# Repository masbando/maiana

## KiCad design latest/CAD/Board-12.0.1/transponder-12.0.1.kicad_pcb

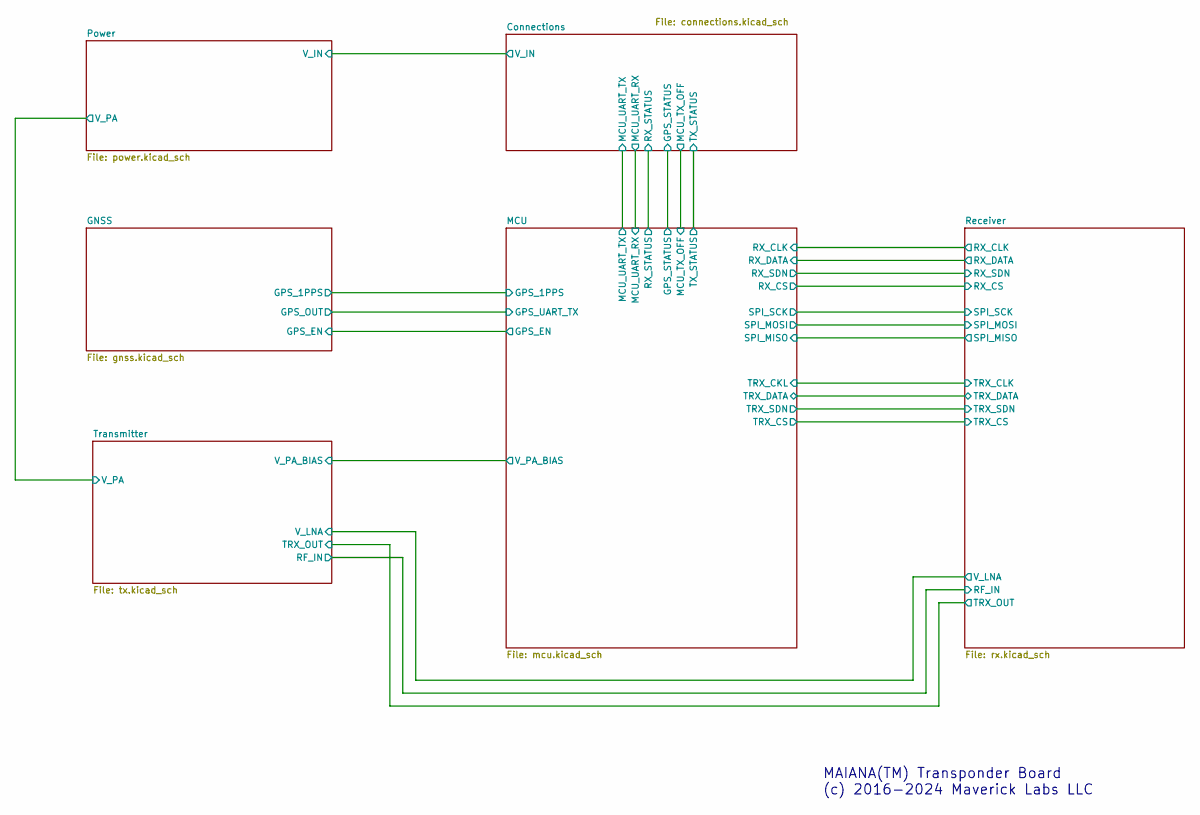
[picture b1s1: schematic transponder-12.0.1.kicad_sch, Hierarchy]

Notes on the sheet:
MAIANA(TM) Transponder Board (c) 2016-2024 Maverick Labs LLC

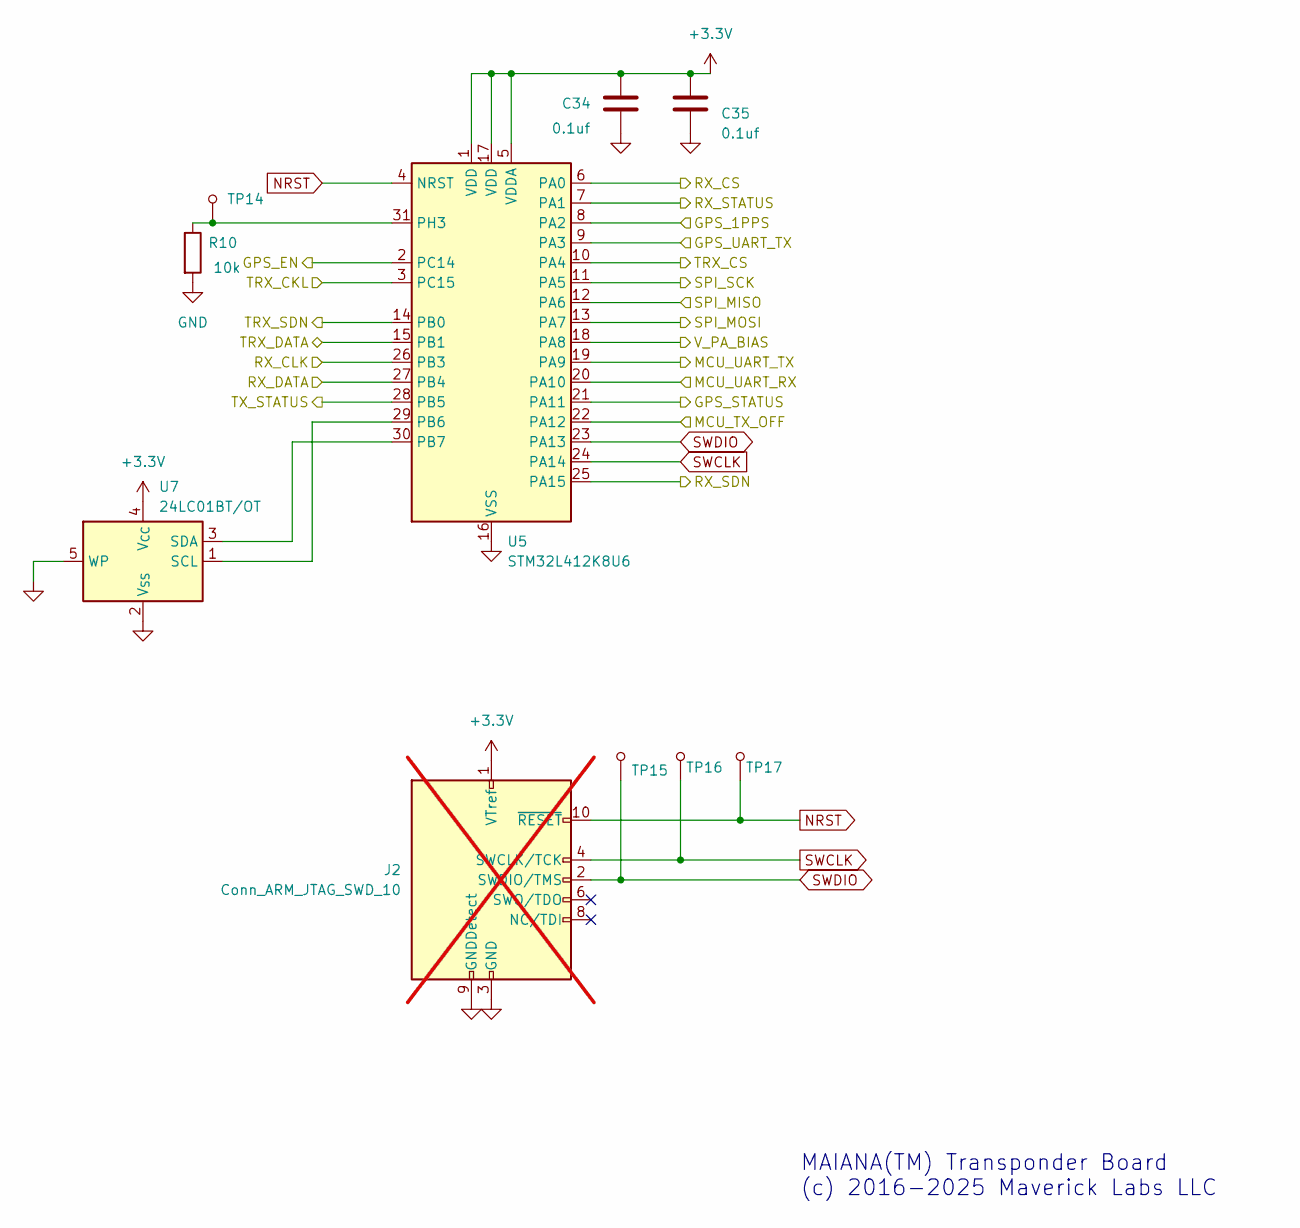
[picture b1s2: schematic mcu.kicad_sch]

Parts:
C34, C35: 0.1uf; C_0603_1608Metric
J2: Conn_ARM_JTAG_SWD_10; PinHeader_2x05_P1.27mm_Vertical_SMD; not fitted
R10: 10k; R_0603_1608Metric
TP14, TP15, TP16, TP17: TP_1.2MM
U5: STM32L412K8U6; QFN-32-1EP_5x5mm_P0.5mm_EP3.45x3.45mm
U7: 24LC01BT/OT; SOT-23-5

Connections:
+3.3V: C34.2, C35.2, J2.1 (VTref), U5.1 (VDD), U5.5 (VDDA), U5.17 (VDD), U7.4 (V_{CC}); also elsewhere on the board
/Connections/GPS_STATUS: U5.21 (PA11); also elsewhere on the board
/Connections/MCU_TX_OFF: U5.22 (PA12); also elsewhere on the board
/Connections/MCU_UART_RX: U5.20 (PA10); also elsewhere on the board
/Connections/MCU_UART_TX: U5.19 (PA9); also elsewhere on the board
/Connections/RX_STATUS: U5.7 (PA1); also elsewhere on the board
/Connections/TX_STATUS: U5.28 (PB5); also elsewhere on the board
/GNSS/GPS_1PPS: U5.8 (PA2); also elsewhere on the board
/GNSS/GPS_EN: U5.2 (PC14); also elsewhere on the board
/GNSS/GPS_OUT: U5.9 (PA3); also elsewhere on the board
/MCU/RX_CLK: U5.26 (PB3); also elsewhere on the board
/MCU/RX_CS: U5.6 (PA0); also elsewhere on the board
/MCU/RX_DATA: U5.27 (PB4); also elsewhere on the board
/MCU/RX_SDN: U5.25 (PA15); also elsewhere on the board
/MCU/SPI_MISO: U5.12 (PA6); also elsewhere on the board
/MCU/SPI_MOSI: U5.13 (PA7); also elsewhere on the board
/MCU/SPI_SCK: U5.11 (PA5); also elsewhere on the board
/MCU/TRX_CKL: U5.3 (PC15); also elsewhere on the board
/MCU/TRX_CS: U5.10 (PA4); also elsewhere on the board
/MCU/TRX_DATA: U5.15 (PB1); also elsewhere on the board
/MCU/TRX_SDN: U5.14 (PB0); also elsewhere on the board
/MCU/V_PA_BIAS: U5.18 (PA8); also elsewhere on the board
GND: C34.1, C35.1, J2.3 (GND), J2.5 (GND), J2.9 (GNDDetect), R10.2, U5.16 (VSS), U5.32 (VSS), U5.33 (VSS), U7.2 (V_{SS}), U7.5 (WP); also elsewhere on the board
NRST: J2.10 (~RESET), TP17.1, U5.4 (NRST)
unnamed: R10.1, TP14.1, U5.31 (PH3)
unnamed: U5.29 (PB6), U7.1 (SCL)
unnamed: U5.30 (PB7), U7.3 (SDA)
SWCLK: J2.4 (SWCLK/TCK), TP16.1, U5.24 (PA14)
SWDIO: J2.2 (SWDIO/TMS), TP15.1, U5.23 (PA13)

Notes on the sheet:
MAIANA(TM) Transponder Board (c) 2016-2025 Maverick Labs LLC

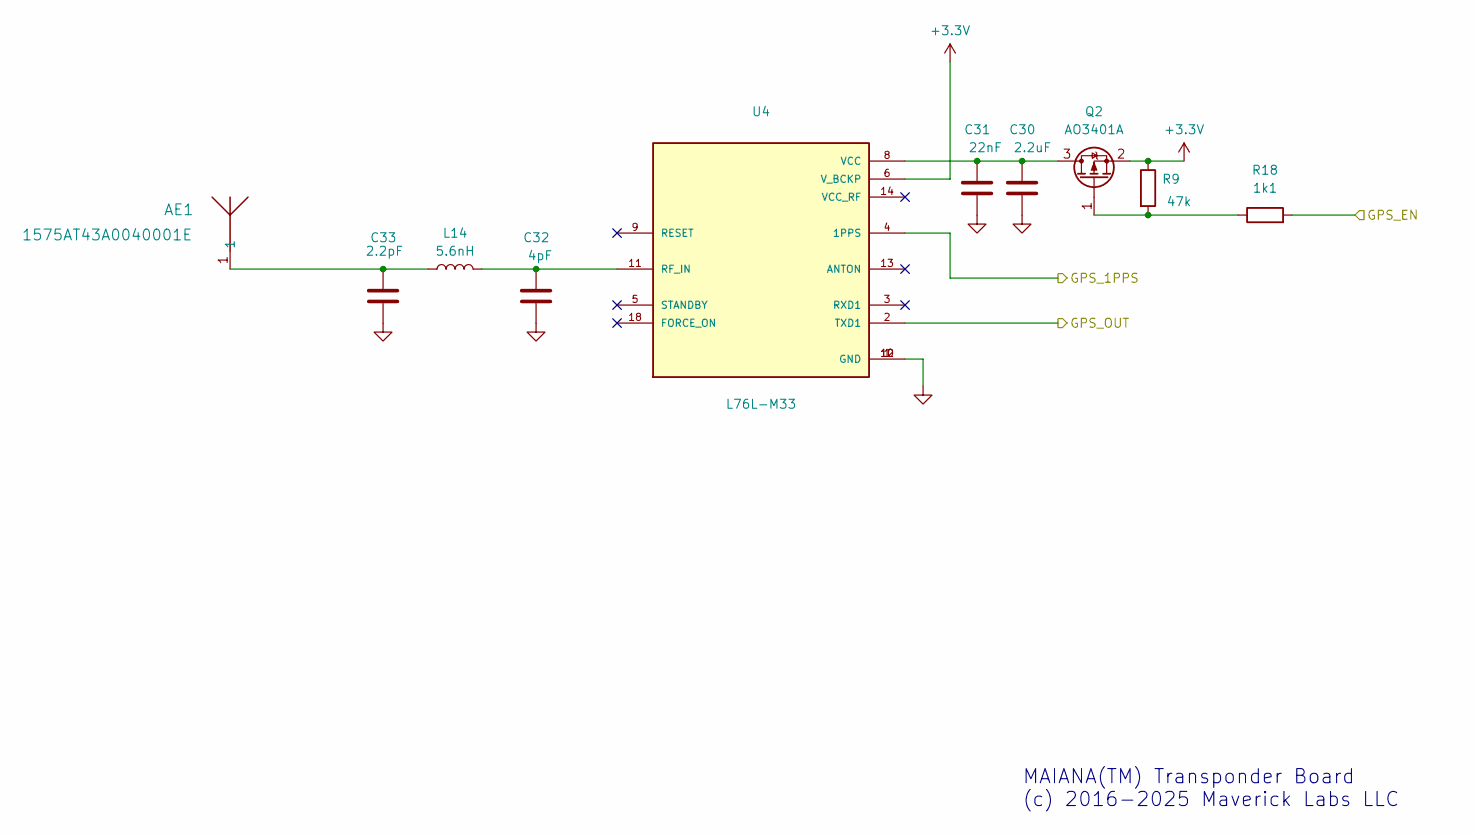
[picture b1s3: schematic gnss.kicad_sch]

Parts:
AE1: 1575AT43A0040001E; ANT_1575AT_JOT
C30: 2.2uF; C_0603_1608Metric
C31: 22nF; C_0603_1608Metric
C32: 4pF; C_0603_1608Metric
C33: 2.2pF; C_0603_1608Metric
L14: 5.6nH; L_0603_1608Metric
Q2: AO3401A; SOT-23
R9: 47k; R_0603_1608Metric
R18: 1k1; R_0603_1608Metric
U4: L76L-M33; XCVR_L76L-M33

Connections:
+3.3V: Q2.2 (S), R9.1, U4.6 (V_BCKP); also elsewhere on the board
/GNSS/GPS_1PPS: U4.4 (1PPS); also elsewhere on the board
/GNSS/GPS_EN: R18.2; also elsewhere on the board
/GNSS/GPS_OUT: U4.2 (TXD1); also elsewhere on the board
GND: C30.1, C31.1, C32.1, C33.1, U4.1 (GND), U4.10 (GND), U4.12 (GND); also elsewhere on the board
unnamed: AE1.1, C33.2, L14.1
unnamed: C30.2, C31.2, Q2.3 (D), U4.8 (VCC)
unnamed: Q2.1 (G), R9.2, R18.1
unnamed: C32.2, L14.2, U4.11 (RF_IN)

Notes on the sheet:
MAIANA(TM) Transponder Board (c) 2016-2025 Maverick Labs LLC

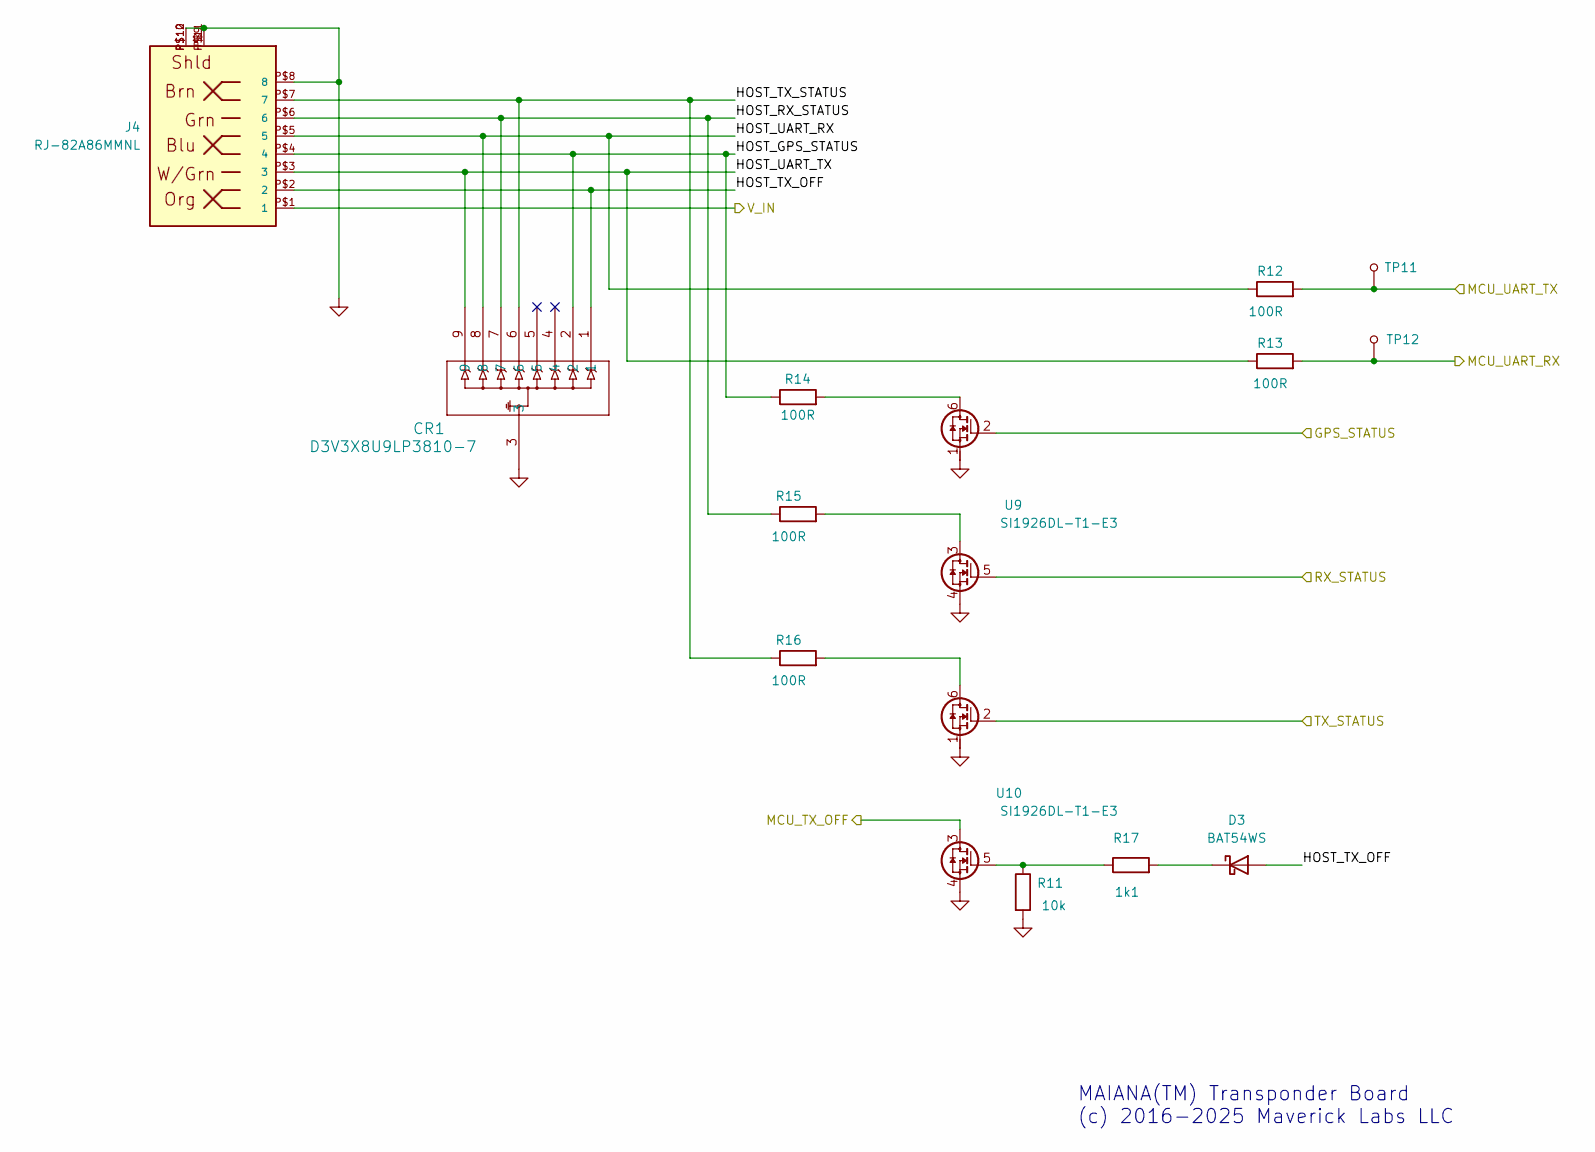
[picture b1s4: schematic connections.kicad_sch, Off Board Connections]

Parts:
CR1: D3V3X8U9LP3810-7; U-DFN3810-9TYPE_B_DIO
D3: BAT54WS; D_SOD-323
J4: RJ-82A86MMNL; PARTNO RJ-82A86MMNL
R11: 10k; R_0603_1608Metric
R12, R13, R14, R15, R16: 100R; R_0603_1608Metric
R17: 1k1; R_0603_1608Metric
TP11, TP12: TP_1.2MM
U9, U10: SI1926DL-T1-E3; SOT-363_SC-70-6

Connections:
/Connections/GPS_STATUS: U9.2 (G1); also elsewhere on the board
/Connections/HOST_GPS_STATUS: CR1.2, J4.P$4 (4), R14.1
/Connections/HOST_RX_STATUS: CR1.7, J4.P$6 (6), R15.1
/Connections/HOST_TX_OFF: CR1.1, D3.2 (A), J4.P$2 (2)
/Connections/HOST_TX_STATUS: CR1.6, J4.P$7 (7), R16.1
/Connections/HOST_UART_RX: CR1.8, J4.P$5 (5), R12.1
/Connections/HOST_UART_TX: CR1.9, J4.P$3 (3), R13.1
/Connections/MCU_TX_OFF: U10.3 (D2); also elsewhere on the board
/Connections/MCU_UART_RX: R13.2, TP12.1; also elsewhere on the board
/Connections/MCU_UART_TX: R12.2, TP11.1; also elsewhere on the board
/Connections/RX_STATUS: U9.5 (G2); also elsewhere on the board
/Connections/TX_STATUS: U10.2 (G1); also elsewhere on the board
/Connections/V_IN: J4.P$1 (1); also elsewhere on the board
GND: CR1.3, J4.P$8 (8), J4.P$9, J4.P$10, J4.P$11, J4.P$12, R11.2, U9.1 (S1), U9.4 (S2), U10.1 (S1), U10.4 (S2); also elsewhere on the board
unnamed: D3.1 (K), R17.2
unnamed: R14.2, U9.6 (D1)
unnamed: R15.2, U9.3 (D2)
unnamed: R16.2, U10.6 (D1)
unnamed: R11.1, R17.1, U10.5 (G2)

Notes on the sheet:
MAIANA(TM) Transponder Board (c) 2016-2025 Maverick Labs LLC

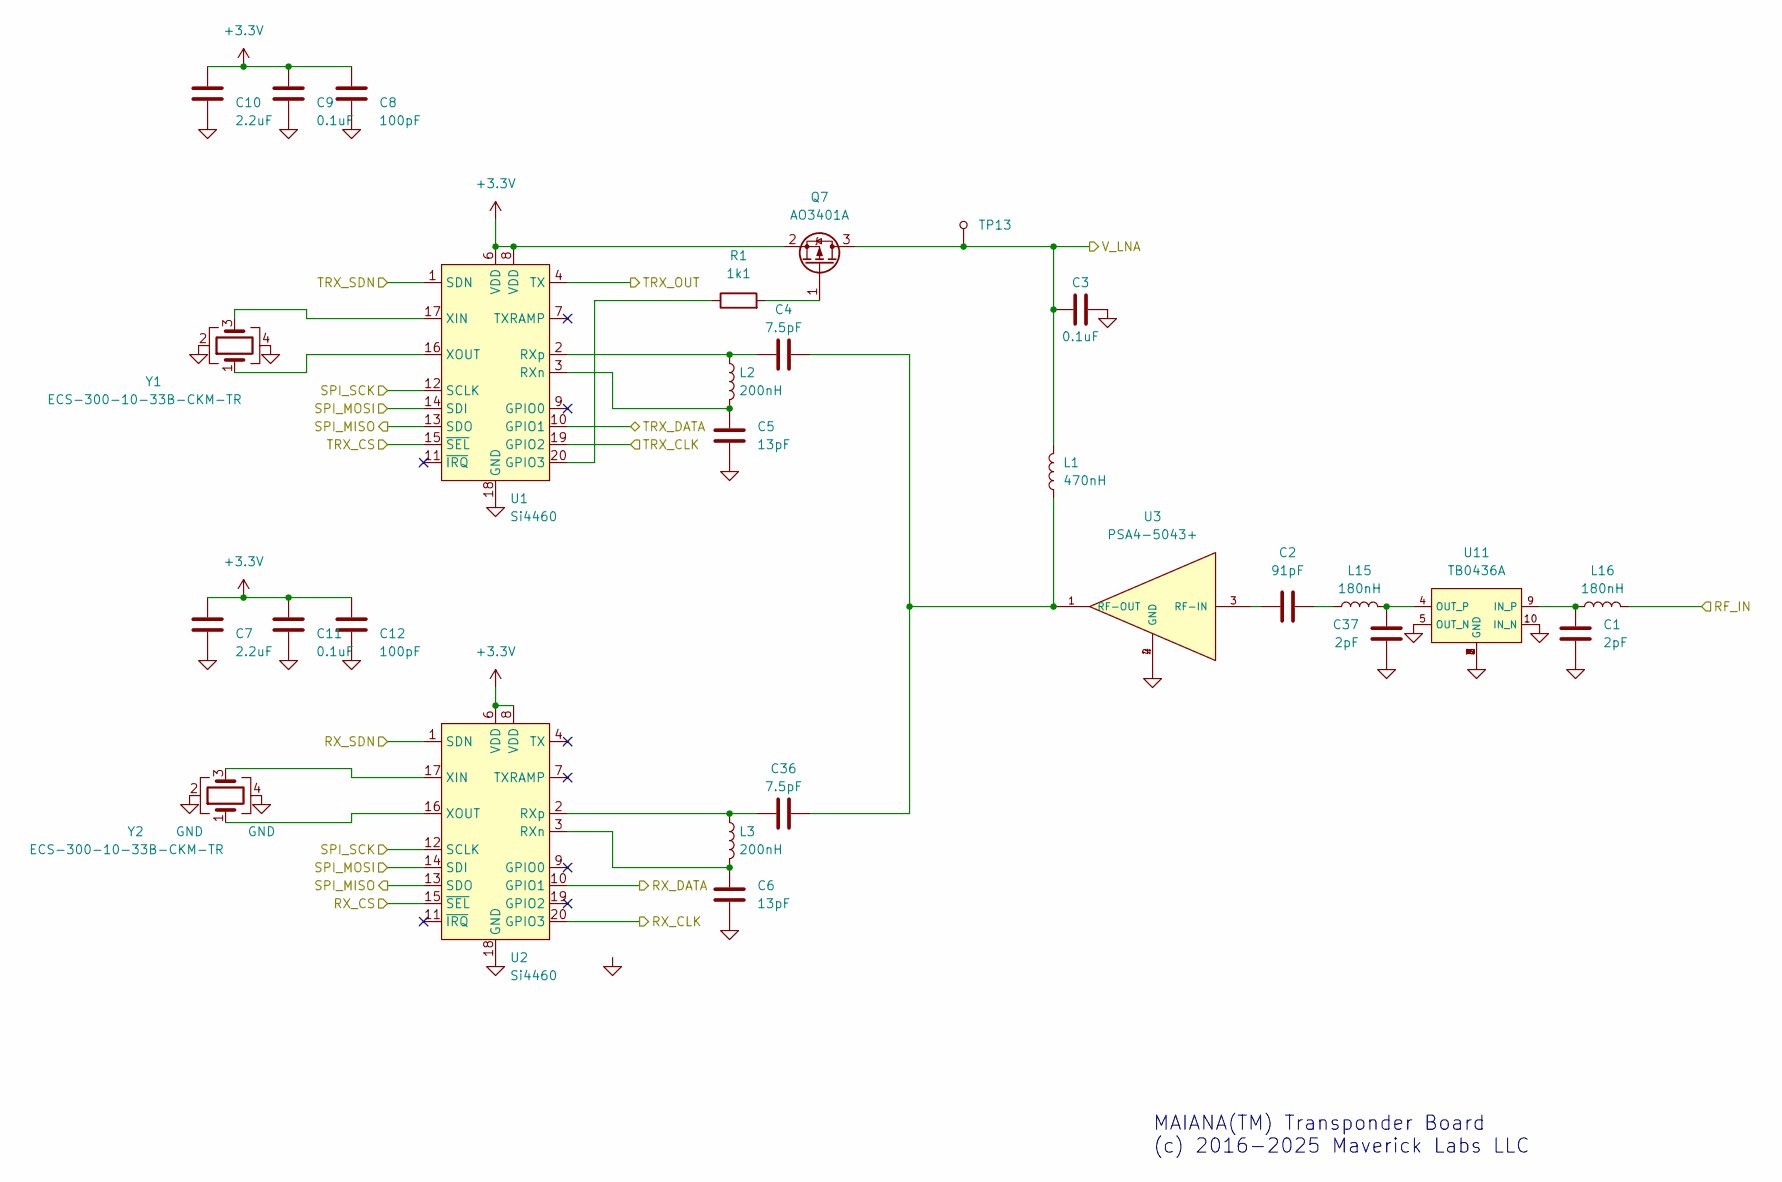
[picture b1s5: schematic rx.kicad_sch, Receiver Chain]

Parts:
C1, C37: 2pF; C_0603_1608Metric
C2: 91pF; C_0603_1608Metric
C3, C9, C11: 0.1uF; C_0603_1608Metric
C4, C36: 7.5pF; C_0402_1005Metric
C5, C6: 13pF; C_0402_1005Metric
C7, C10: 2.2uF; C_0603_1608Metric
C8, C12: 100pF; C_0603_1608Metric
L1: 470nH; L_0603_1608Metric
L2, L3: 200nH; L_0402_1005Metric
L15, L16: 180nH; L_0603_1608Metric
Q7: AO3401A; SOT-23
R1: 1k1; R_0603_1608Metric
TP13: TP_1.2MM
U1, U2: Si4460; QFN-20-1EP_4x4mm_P0.5mm_EP2.6x2.6mm_ThermalVias
U3: PSA4-5043+; PSA4-5043_
U11: TB0436A
Y1, Y2: ECS-300-10-33B-CKM-TR; Crystal_SMD_3225-4Pin_3.2x2.5mm

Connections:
+3.3V: C7.2, C8.2, C9.2, C10.2, C11.2, C12.2, Q7.2 (S), U1.6 (VDD), U1.8 (VDD), U2.6 (VDD), U2.8 (VDD); also elsewhere on the board
/MCU/RX_CLK: U2.20 (GPIO3); also elsewhere on the board
/MCU/RX_CS: U2.15 (~SEL); also elsewhere on the board
/MCU/RX_DATA: U2.10 (GPIO1); also elsewhere on the board
/MCU/RX_SDN: U2.1 (SDN); also elsewhere on the board
/MCU/SPI_MISO: U1.13 (SDO), U2.13 (SDO); also elsewhere on the board
/MCU/SPI_MOSI: U1.14 (SDI), U2.14 (SDI); also elsewhere on the board
/MCU/SPI_SCK: U1.12 (SCLK), U2.12 (SCLK); also elsewhere on the board
/MCU/TRX_CKL: U1.19 (GPIO2); also elsewhere on the board
/MCU/TRX_CS: U1.15 (~SEL); also elsewhere on the board
/MCU/TRX_DATA: U1.10 (GPIO1); also elsewhere on the board
/MCU/TRX_SDN: U1.1 (SDN); also elsewhere on the board
/Receiver/RF_IN: L16.2; also elsewhere on the board
/Receiver/TRX_OUT: U1.4 (TX); also elsewhere on the board
/Receiver/V_LNA: C3.1, L1.2, Q7.3 (D), TP13.1; also elsewhere on the board
GND: C1.2, C3.2, C5.2, C6.2, C7.1, C8.1, C9.1, C10.1, C11.1, C12.1, C37.2, U1.18 (GND), U1.21 (GND), U2.18 (GND), U2.21 (GND), U3.2 (GND), U3.4 (GND), U11.1, U11.2 (GND), U11.3, U11.5 (OUT_N), U11.6, U11.7, U11.8, U11.10 (IN_N), Y1.2, Y1.4, Y2.2, Y2.4; also elsewhere on the board
unnamed: C2.2, L15.1
unnamed: Q7.1 (G), R1.2
unnamed: R1.1, U1.20 (GPIO3)
unnamed: C5.1, L2.2, U1.3 (RXn)
unnamed: C4.1, L2.1, U1.2 (RXp)
unnamed: U1.17 (XIN), Y1.3
unnamed: U1.16 (XOUT), Y1.1
unnamed: C6.1, L3.2, U2.3 (RXn)
unnamed: C36.1, L3.1, U2.2 (RXp)
unnamed: U2.17 (XIN), Y2.3
unnamed: U2.16 (XOUT), Y2.1
unnamed: C2.1, U3.3 (RF-IN)
unnamed: C4.2, C36.2, L1.1, U3.1 (RF-OUT)
unnamed: C1.1, L16.1, U11.9 (IN_P)
unnamed: C37.1, L15.2, U11.4 (OUT_P)

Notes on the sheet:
MAIANA(TM) Transponder Board (c) 2016-2025 Maverick Labs LLC

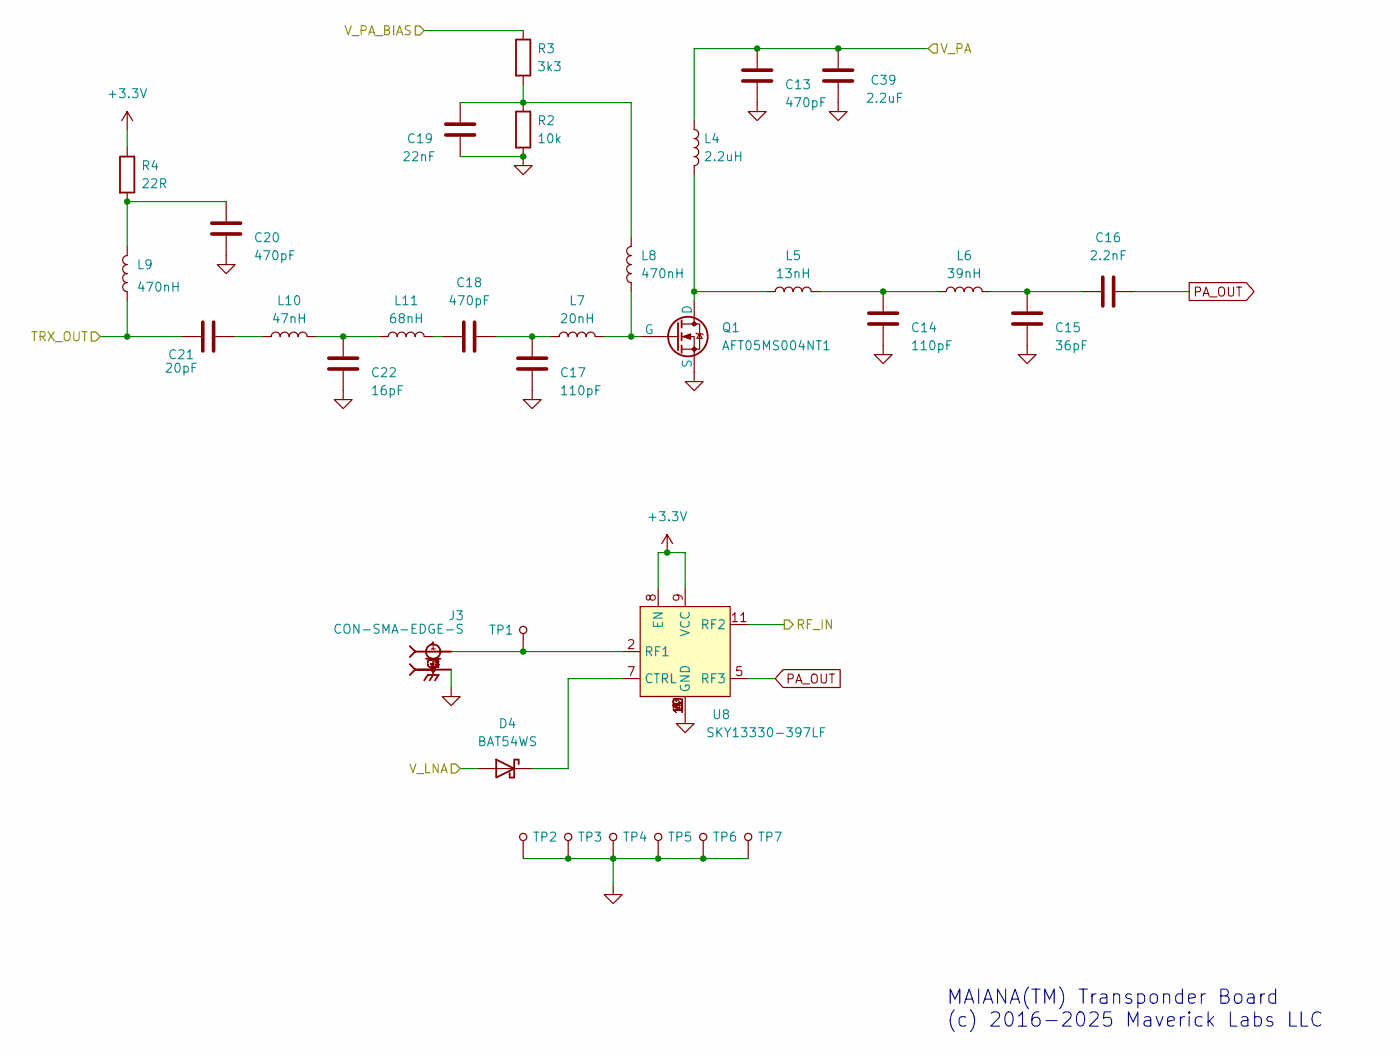
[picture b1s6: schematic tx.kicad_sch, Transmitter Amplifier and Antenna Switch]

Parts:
C13, C18, C20: 470pF; C_0603_1608Metric
C14, C17: 110pF; C_0603_1608Metric
C15: 36pF; C_0603_1608Metric
C16: 2.2nF; C_0603_1608Metric
C19: 22nF; C_0603_1608Metric
C21: 20pF; C_0603_1608Metric
C22: 16pF; C_0603_1608Metric
C39: 2.2uF; C_0603_1608Metric
D4: BAT54WS; D_SOD-323
J3: CON-SMA-EDGE-S; RFSOLUTIONS_CON-SMA-EDGE-S; PARTREV 1; DigiKey_Part_Number CON-SMA-EDGE-S-ND
L4: 2.2uH; L_0603_1608Metric
L5: 13nH; L_0603_1608Metric
L6: 39nH; L_0603_1608Metric
L7: 20nH; L_0603_1608Metric
L8, L9: 470nH; L_0603_1608Metric
L10: 47nH; L_0603_1608Metric
L11: 68nH; L_0603_1608Metric
Q1: AFT05MS004NT1; SOT-89-3
R2: 10k; R_0603_1608Metric
R3: 3k3; R_0603_1608Metric
R4: 22R; R_0603_1608Metric
TP1: TP_1.0MM
TP2, TP3, TP4, TP5, TP6, TP7: TP_1.2MM
U8: SKY13330-397LF; QFN50P200X200X65-13N

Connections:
+3.3V: R4.1, U8.8 (EN), U8.9 (VCC); also elsewhere on the board
/MCU/V_PA_BIAS: R3.1; also elsewhere on the board
/Power/V_PA: C13.2, C39.2, L4.1; also elsewhere on the board
/Receiver/RF_IN: U8.11 (RF2); also elsewhere on the board
/Receiver/TRX_OUT: C21.1, L9.1; also elsewhere on the board
/Receiver/V_LNA: D4.2 (A); also elsewhere on the board
GND: C13.1, C14.1, C15.1, C17.1, C19.1, C20.1, C22.1, C39.1, J3.G1, J3.G2, J3.G3, J3.G4, Q1.2 (S), R2.2, TP2.1, TP3.1, TP4.1, TP5.1, TP6.1, TP7.1, U8.1 (GND), U8.3 (GND), U8.4 (GND), U8.6 (GND), U8.10 (GND), U8.12 (GND), U8.13 (GND); also elsewhere on the board
unnamed: C14.2, L5.2, L6.1
unnamed: C15.2, C16.1, L6.2
unnamed: C17.2, C18.2, L7.1
unnamed: C18.1, L11.2
unnamed: C19.2, L8.2, R2.1, R3.2
unnamed: C20.2, L9.2, R4.2
unnamed: C21.2, L10.1
unnamed: C22.2, L10.2, L11.1
unnamed: D4.1 (K), U8.7 (CTRL)
unnamed: L4.2, L5.1, Q1.3 (D)
unnamed: L7.2, L8.1, Q1.1 (G)
unnamed: J3.1, TP1.1, U8.2 (RF1)
PA_OUT: C16.2, U8.5 (RF3)

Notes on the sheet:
MAIANA(TM) Transponder Board (c) 2016-2025 Maverick Labs LLC

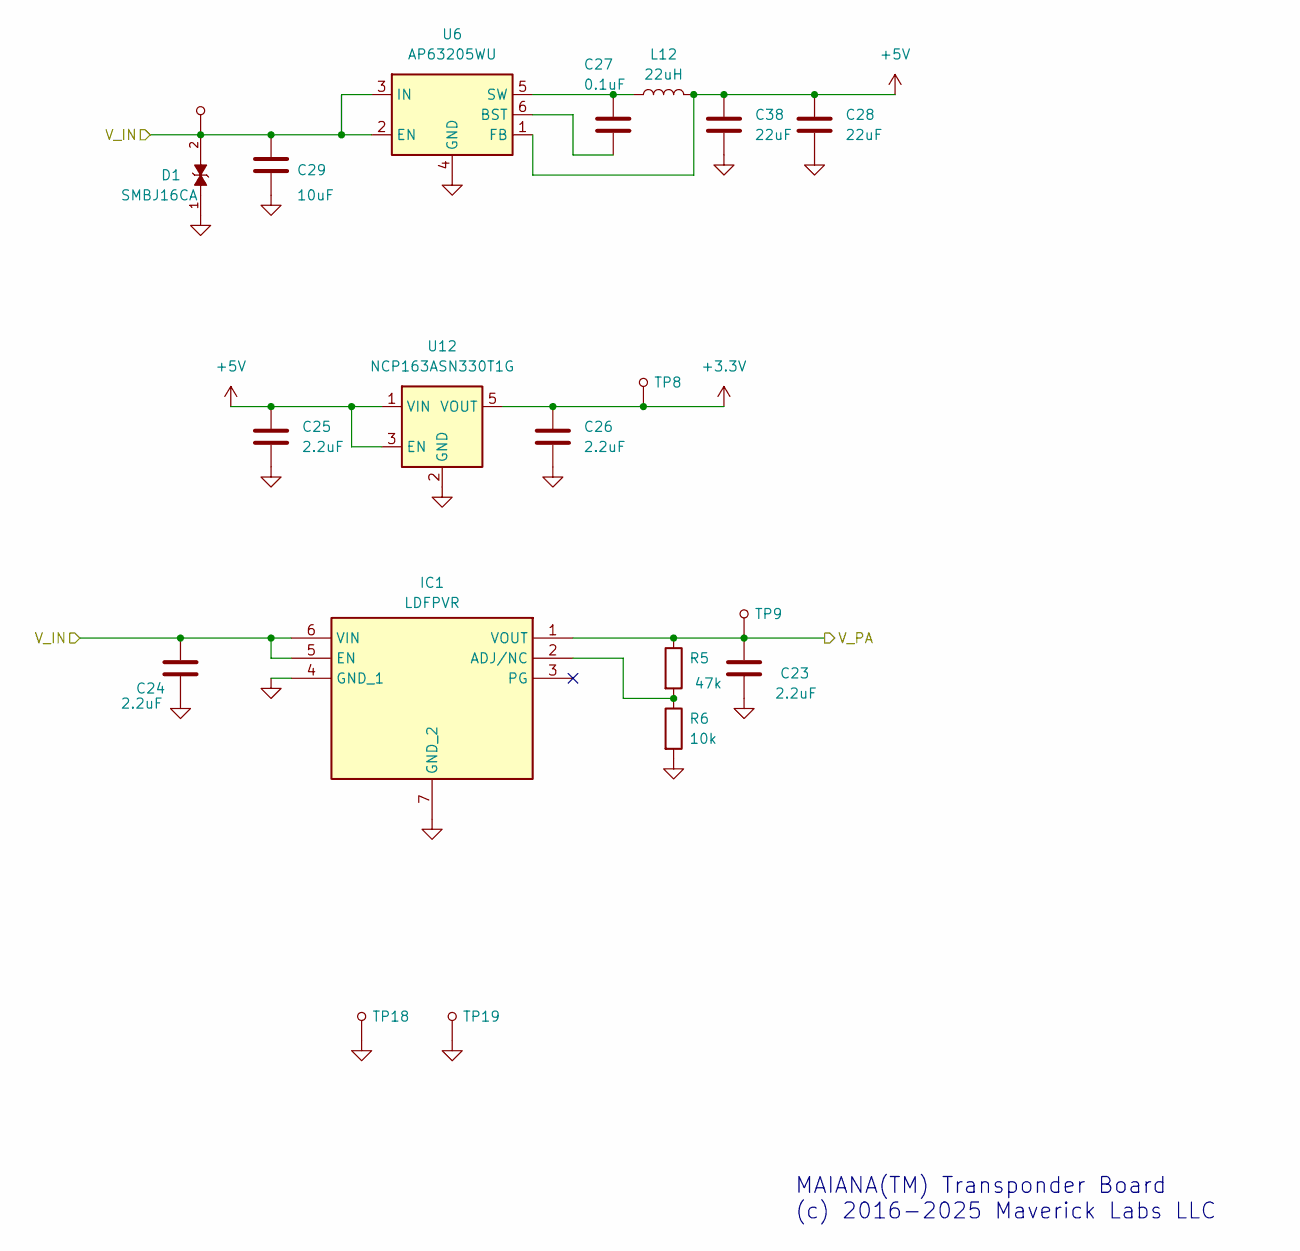
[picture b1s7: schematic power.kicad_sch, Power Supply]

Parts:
C23, C24, C25, C26: 2.2uF; C_0603_1608Metric
C27: 0.1uF; C_0603_1608Metric
C28, C38: 22uF; C_0805_2012Metric
C29: 10uF; C_0805_2012Metric
D1: SMBJ16CA; DIOM4336X265N; PARTREV I2102
IC1: LDFPVR; SON65P200X200X100-7N-D; Mouser Part Number 511-LDFPVR
L12: 22uH; L_1210_3225Metric
R5: 47k; R_0603_1608Metric
R6: 10k; R_0603_1608Metric
TP8, TP9, TP10, TP18, TP19: TP_1.2MM
U6: AP63205WU; TSOT-23-6
U12: NCP163ASN330T1G; SOT-23-5

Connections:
+3.3V: C26.1, TP8.1, U12.5 (VOUT); also elsewhere on the board
+5V: C25.1, C28.1, C38.1, L12.2, U6.1 (FB), U12.1 (VIN), U12.3 (EN)
/Connections/V_IN: C24.2, C29.1, D1.2, IC1.5 (EN), IC1.6 (VIN), TP10.1, U6.2 (EN), U6.3 (IN); also elsewhere on the board
/Power/V_PA: C23.2, IC1.1 (VOUT), R5.1, TP9.1; also elsewhere on the board
GND: C23.1, C24.1, C25.2, C26.2, C28.2, C29.2, C38.2, D1.1, IC1.4 (GND_1), IC1.7 (GND_2), R6.2, TP18.1, TP19.1, U6.4 (GND), U12.2 (GND); also elsewhere on the board
unnamed: IC1.2 (ADJ/NC), R5.2, R6.1
unnamed: C27.1, U6.6 (BST)
unnamed: C27.2, L12.1, U6.5 (SW)

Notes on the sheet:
MAIANA(TM) Transponder Board (c) 2016-2025 Maverick Labs LLC

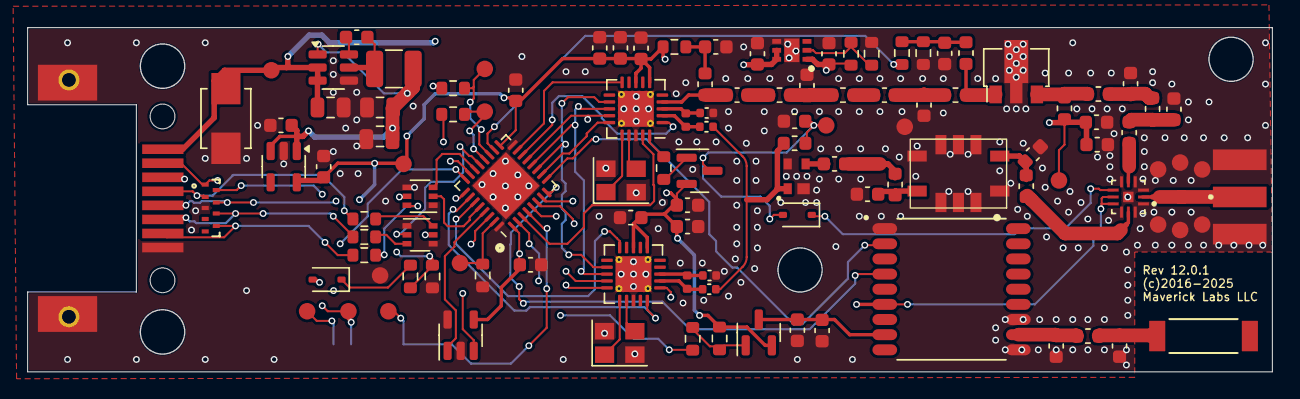
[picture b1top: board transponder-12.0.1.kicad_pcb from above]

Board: 4 copper layers, 90.3 x 24.9 mm, 115 parts (1 on the bottom side), 81 nets.

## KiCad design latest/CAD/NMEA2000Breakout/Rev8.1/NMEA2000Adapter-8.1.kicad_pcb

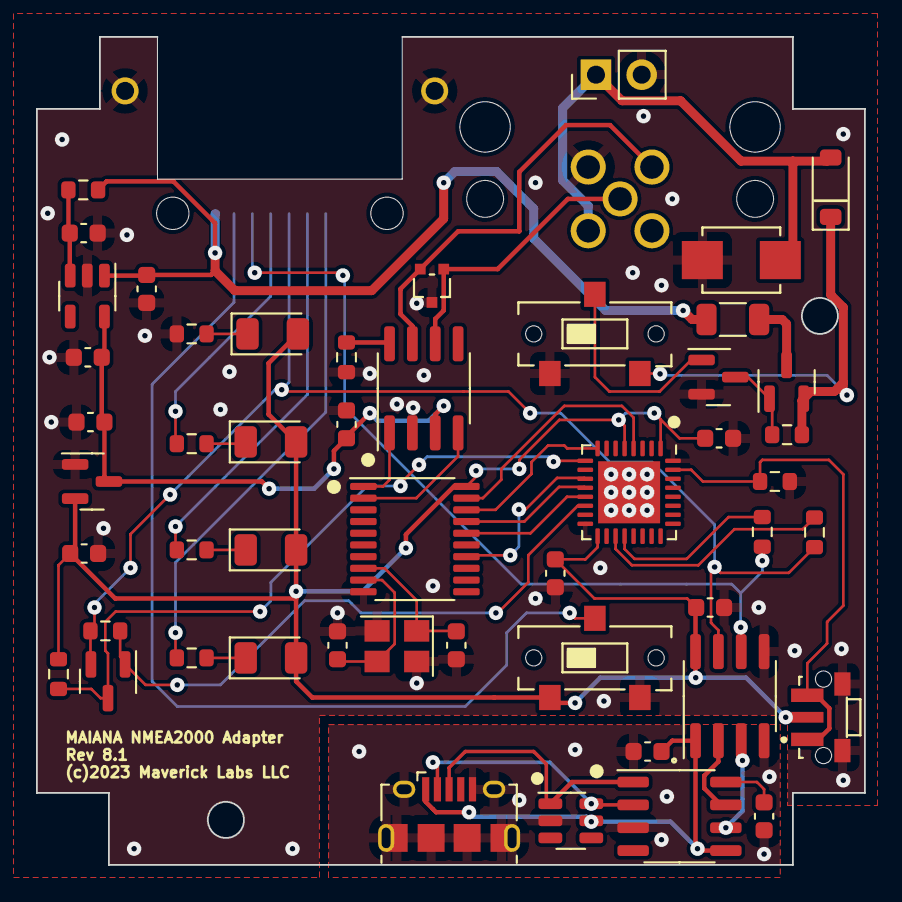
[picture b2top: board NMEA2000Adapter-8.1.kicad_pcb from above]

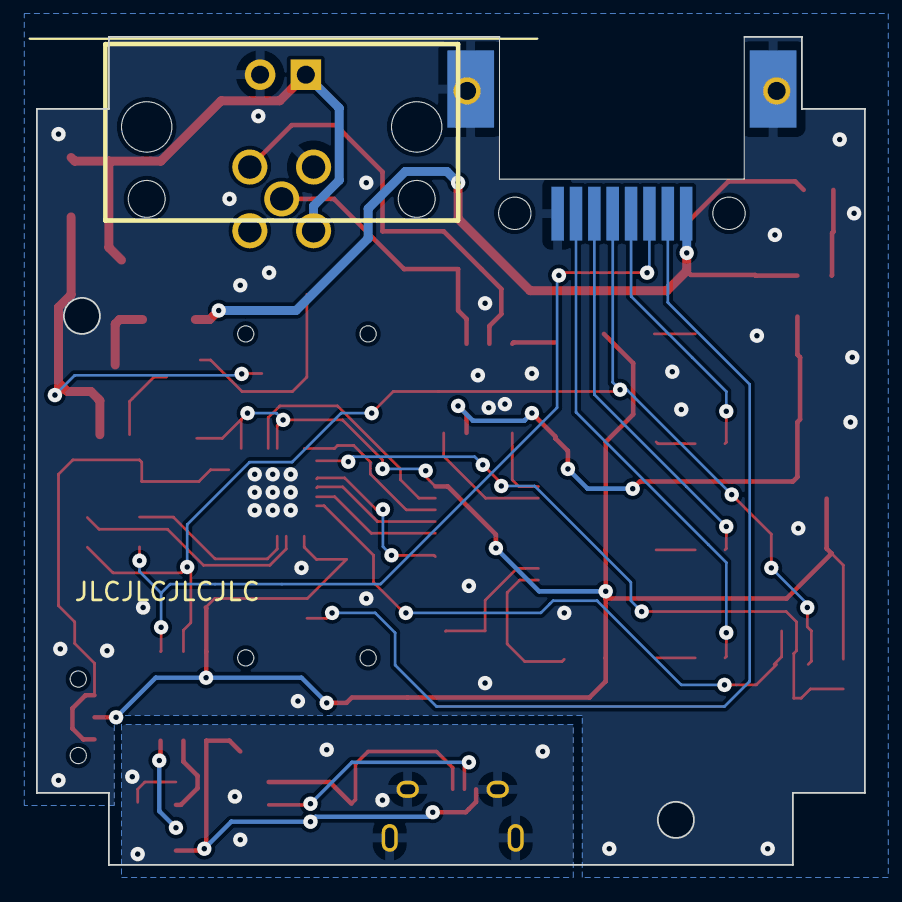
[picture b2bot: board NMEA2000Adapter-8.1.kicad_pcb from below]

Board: 2 copper layers, 46.0 x 46.0 mm, 52 parts (2 on the bottom side), 44 nets.

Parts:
C1, C2, C3, C11, C12, C13: 0.1uF; C_0603_1608Metric
C4, C5: 20pF; C_0603_1608Metric
C6, C7, C8, C9, C10: 1uF; C_0603_1608Metric
D1, D2, D3, D4: LED; LED_1206_3216Metric
D5: PESD1CAN-U; SOT323
D6: SMBJ16CA; DIOM4336X265N
D8: D_Schottky; D_SOD-123
J1: 12-3701-05; MICRO_C_5PIN
J2: RJ-82A86MMNL
J3: USB_B_Micro; USB_Micro-B_Amphenol_10118194_Horizontal
J4: Conn_01x02; PinHeader_1x02_P2.54mm_Vertical
Q1, Q3: BSS138; SOT-23
Q2: AO3401A; SOT-23
R1, R2, R3, R4: 2k2; R_0603_1608Metric
R5, R6, R7, R8, R9, R10: 10k; R_0603_1608Metric
R11, R12: 0R; R_0603_1608Metric
SW1, SW2: CL-SB-12B-01T
SW3: TS-1814; TE_1977066-1
TH1: BSMD1206-050-16V; R_1206_3216Metric
U1: STM32L432KBUx; QFN-32-1EP_5x5mm_P0.5mm_EP3.45x3.45mm
U2: MCP2515-xST; TSSOP-20_4.4x6.5mm_P0.65mm
U3: MCP2551-I-SN; SOIC-8_3.9x4.9mm_P1.27mm
U4: SRV05-4; SOT-23-6
U5: CH340N; SO-8_3.9x4.9mm_P1.27mm
U6: ISO7721DR; SOIC-8_3.9x4.9mm_P1.27mm
U7: TJ5205SF5-5.0; SOT-23-5
U8: SE8533X2-HF; SOT-23
Y1: X322516MOB4SI; Crystal_SMD_3225-4Pin_3.2x2.5mm

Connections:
+3.3V: C2.1, C10.1, C12.1, C13.1, D1.2 (A), D2.2 (A), D3.2 (A), D4.2 (A), R10.1, SW2.1, SW3.2, U1.1 (VDD), U1.5 (VDDA), U1.17 (VDD), U2.20 (VDD), U6.8 (VDD2), U8.2 (VO)
+5V: C8.1, C9.1, C11.1, U3.3 (VDD), U7.5 (OUT), U8.3 (VI)
+12V: D6.2, D8.2 (A), J1.2, J4.1
/CAN/CAN_H: D5.2, J1.4, U3.7 (CANH)
/CAN/CAN_L: D5.1, J1.5, U3.6 (CANL)
/CAN/NRST: U1.4 (NRST), U2.19 (~RESET)
/CAN/SPI_CS: U1.8 (PA2), U2.18 (~CS)
/CAN/SPI_MISO: U1.12 (PA6), U2.17 (SO)
/CAN/SPI_MOSI: U1.13 (PA7), U2.16 (SI)
/CAN/SPI_SCK: U1.11 (PA5), U2.14 (SCK)
/Connections/AIS_RX_EVENT: J2.P$6 (6), R3.2
/Connections/AIS_TX_EVENT: J2.P$7 (7), R4.2
/Connections/GPS_STATUS: J2.P$4 (4), R2.2
/Connections/MCU_UART_RX: R12.2, U1.20 (PA10)
/Connections/MCU_UART_TX: R11.2, U1.19 (PA9)
/Connections/TRANSPONDER_UART_TX: J2.P$5 (5), Q3.2 (S), R9.2, R11.1, U6.7 (VIA)
/Connections/TX_DISABLE: J2.P$2 (2), SW2.C
/Connections/V_OUT: C7.1, J2.P$1 (1), R6.1, TH1.1, U7.1 (IN)
/MCU/BOOT0: R8.1, SW3.1, SW3.3, U1.31 (PH3)
/Power/PWR_CTRL: Q1.1 (G), SW1.C
/Power/V_IN: D8.1 (K), Q2.2 (S), R5.1, SW1.3
CH340_RX: U5.7 (RX), U6.2 (VOA)
CH340_TX: U5.6 (TX), U6.3 (VIB)
D+: J3.3 (D+), U4.1 (IO1), U5.1 (D+)
D-: J3.2 (D-), U4.6 (IO4), U5.2 (D-)
GND: C2.2, C4.2, C5.2, C6.2, C7.2, C8.2, C9.2, C10.2, C11.2, C12.2, C13.2, D5.3, D6.1, J1.3, J2.P$8 (8), J2.P$9, J2.P$10, J2.P$11, J2.P$12, J4.2, Q1.2 (S), R1.2, R7.2, R8.2, SW1.1, SW2.3, SW3.S1 (SHIELD), SW3.S2 (SHIELD), U1.16 (VSS), U1.32 (VSS), U1.33 (VSS), U2.10 (VSS), U3.2 (VSS), U6.5 (GND2), U7.2 (GND), U8.1 (GND), Y1.2, Y1.4
GND2: C1.2, C3.2, J3.5 (GND), J3.6 (Shield), U4.2 (VN), U5.3 (GND), U6.4 (GND1)
NMEA_RX: Q3.3 (D), R10.2, U1.9 (PA3)
NMEA_RX_EN: Q3.1 (G), R9.1, U1.14 (PB0)
unnamed: D1.1 (K), R1.1
unnamed: D2.1 (K), R2.1
unnamed: D3.1 (K), R3.1
unnamed: D4.1 (K), R4.1
unnamed: Q1.3 (D), Q2.1 (G), R5.2
unnamed: Q2.3 (D), TH1.2
unnamed: U2.2 (RXCAN), U3.4 (RXD)
unnamed: U2.1 (TXCAN), U3.1 (TXD)
unnamed: R7.1, U3.8 (Rs)
unnamed: C1.1, U5.8 (V3)
unnamed: C6.1, R6.2, U7.3 (EN)
TRANSPONDER_UART_RX: J2.P$3 (3), R12.1, U6.6 (VOB)
VBUS: C3.1, J3.1 (VBUS), U4.5 (VP), U5.5 (VCC), U6.1 (VDD1)
XTL1: C5.1, U2.8 (OSC2), Y1.1
XTL2: C4.1, U2.9 (OSC1), Y1.3

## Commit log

2025-10-12 Added board 12.0.1 CAD
2025-10-12 N2K adapter and firmware project update

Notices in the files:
latest/CAD/NMEA2000Breakout/Rev8.1/NMEA2000Adapter-8.1.kicad_pcb:
(c)2023 Maverick Labs LLC
